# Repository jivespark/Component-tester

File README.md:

# Component-tester
This is going to be my project for week 4 of Hack Club halflife. It is a custom board for testing different components. I built this to have a quick way to test circuits, and components. It has 3 modes, continuity testing, analog voltage reading, and digital high/low reading.

## Usage, limitations:
This circuit is designed to handle inputs of no more than 5V, so it is only for testing 5V, and 3.3V logic, nothing higher. uses the RP2040s analog pins for voltage detection, so accuracy also might not be perfect. There are also 3.3V, 5V, and GND output pins, those are for quickly powering breadboard circuits, and components in need of testing. For continuity testing make sure that the circuit is fully unpowered, otherwise, it might fry the pin. To navigate the UI, you need to use the 2 buttons on the side. When in the menu, you can scroll through the options, and select a mode with the bottom button. When in one of the modes, to return to the menu you need to press the top button.

## Assembly:
To assemble, you need to first solder on the resistors, they are designed so you should be able to hand solder them. After that you can solder on the XIAO either SMD or through hole, both should work. For the buttons, you shuld solder them up to their place labeled SW1, and SW2. For the OLED, yo just need to solder it on with a header to the 4 I2C pins up top. On the sides for the headers, you can use either male, or female headers, whichever you like to connect the jumper wires to more.

## Firmware
The latest CircuitPython will need to be downloaded to the XIAO for the code to work. it can be downloaded . The libraries are from the 

Copy everything from the firmware folder onto the board, and it should run.

## Images:

## BOM:
|Item                    |Qty|Supplier  |Cost/item|Total Cost|link                                                 |
|------------------------|---|----------|---------|----------|-----------------------------------------------------|
|Buttons                 |1  |Aliexpress|$2.03    |$2.03     |https://www.aliexpress.com/item/1005003666060830.html|
|XIAO RP2040             |1  |Aliexpress|$1.95    |$1.95     |https://www.aliexpress.com/item/1005013497370642.html|
|128x64 OLED             |1  |Aliexpress|$2.71    |$2.71     |https://www.aliexpress.com/item/1005009170035050.html|
|Resistors               |1  |Aliexpress|$4.29    |$4.29     |https://www.aliexpress.com/item/1005004509226482.html|
|PCB                     |1  |JLCPC     |$2.00    |$2.00     |https://cart.jlcpcb.com/quote                        |
|Estimated total shipping|1  |          |         |$5.76     |                                                     |

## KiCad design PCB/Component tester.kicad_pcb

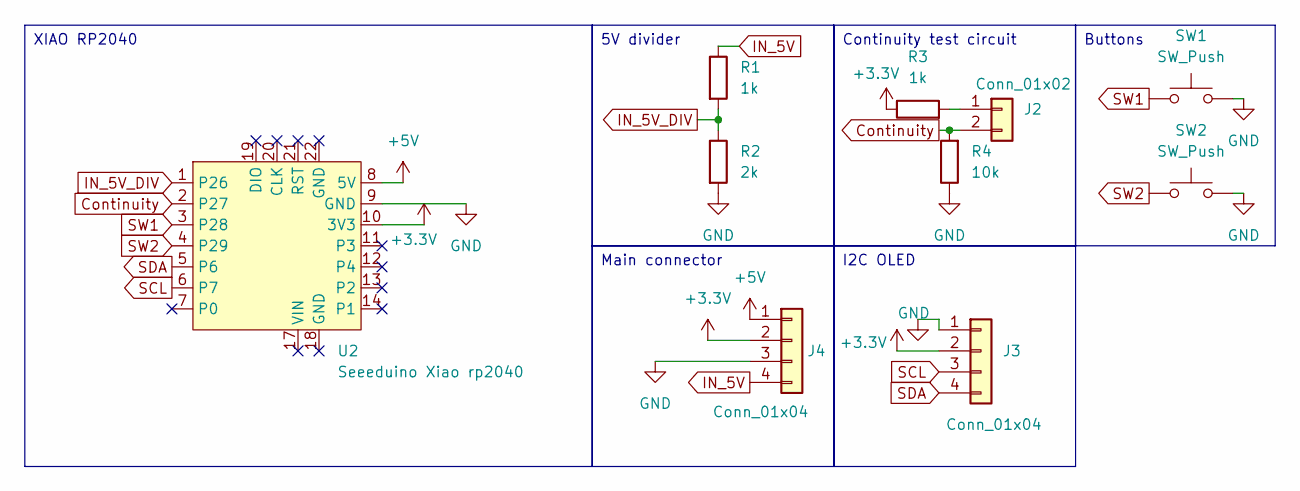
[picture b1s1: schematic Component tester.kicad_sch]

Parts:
J2: Conn_01x02; PinHeader_1x02_P2.54mm_Vertical
J3, J4: Conn_01x04; PinHeader_1x04_P2.54mm_Vertical
R1, R3: 1k; R_0603_1608Metric_Pad0.98x0.95mm_HandSolder
R2: 2k; R_0603_1608Metric_Pad0.98x0.95mm_HandSolder
R4: 10k; R_0603_1608Metric_Pad0.98x0.95mm_HandSolder
SW1, SW2: SW_Push; SW_PUSH_6mm
U2: Seeeduino Xiao rp2040; Xiao_rp2040_ACH

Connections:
+3.3V: J3.2, J4.2, R3.1, U2.10 (3V3)
+5V: J4.1, U2.8 (5V)
Continuity: J2.2, R4.2, U2.2 (P27)
GND: J3.1, J4.3, R2.2, R4.1, SW1.2, SW2.2, U2.9 (GND)
IN_5V: J4.4, R1.1
IN_5V_DIV: R1.2, R2.1, U2.1 (P26)
unnamed: J2.1, R3.2
SCL: J3.3, U2.6 (P7)
SDA: J3.4, U2.5 (P6)
SW1: SW1.1, U2.3 (P28)
SW2: SW2.1, U2.4 (P29)

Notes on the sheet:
I2C OLED
Main connector
XIAO RP2040
Continuity test circuit
5V divider
Buttons

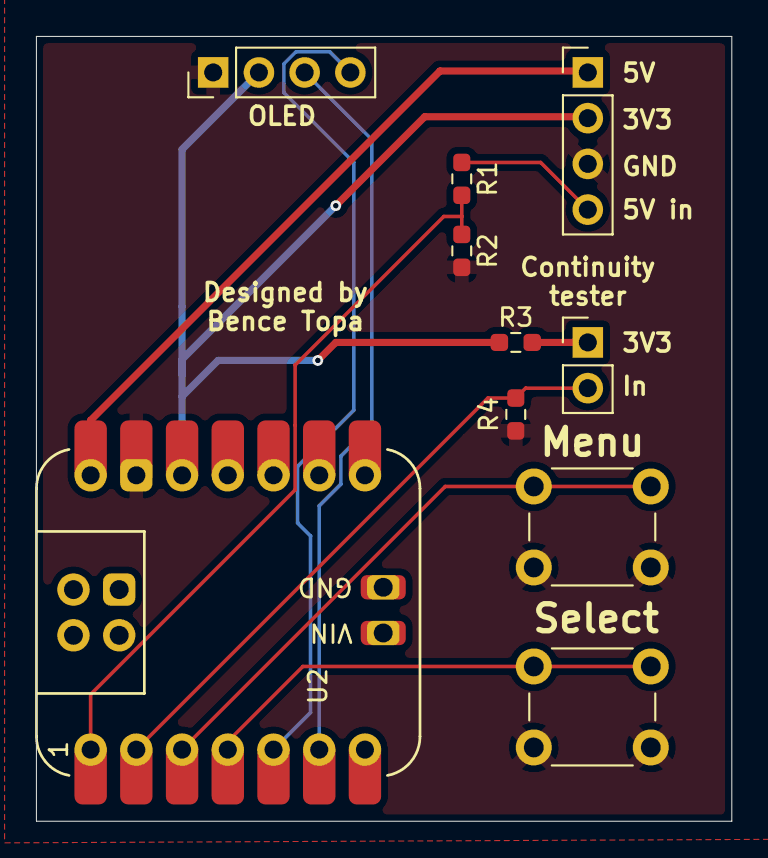
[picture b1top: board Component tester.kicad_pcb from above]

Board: 2 copper layers, 38.6 x 43.6 mm, 10 parts (0 on the bottom side), 11 nets.
